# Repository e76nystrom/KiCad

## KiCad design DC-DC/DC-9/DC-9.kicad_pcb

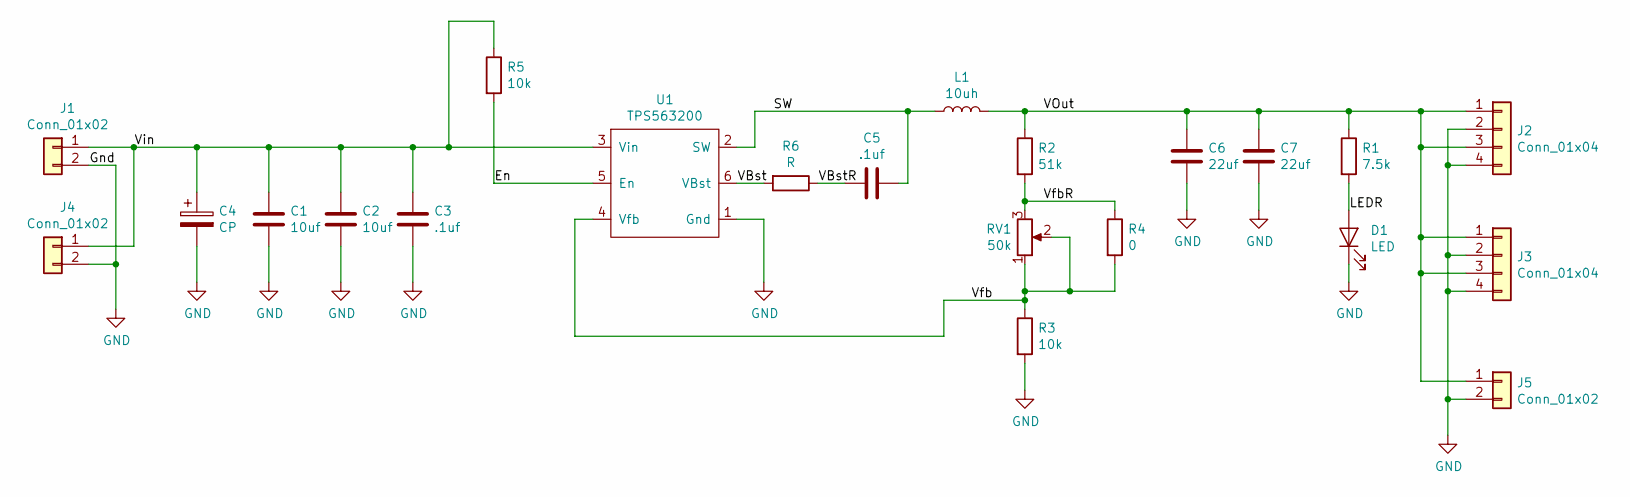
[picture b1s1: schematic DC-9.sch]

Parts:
C1, C2: 10uf; C_0603_1608Metric_Pad1.05x0.95mm_HandSolder
C3, C5: .1uf; C_0805_2012Metric_Pad1.15x1.40mm_HandSolder
C4: CP; CP_Radial_D10.0mm_P5.00mm
C6, C7: 22uf; C_1206_3216Metric_Pad1.42x1.75mm_HandSolder
D1: LED; LED_0805_2012Metric_Pad1.15x1.40mm_HandSolder
J1: Conn_01x02; 2 Pin 3.81mm
J2, J3: Conn_01x04; 4 Pin 3.81mm
J4, J5: Conn_01x02; PinHeader_1x02_P2.54mm_Vertical
L1: 10uh; SRU1038
R1: 7.5k; R_0805_2012Metric_Pad1.15x1.40mm_HandSolder
R2: 51k; R_0805_2012Metric_Pad1.15x1.40mm_HandSolder
R3: 10k; R_0603_1608Metric_Pad1.05x0.95mm_HandSolder
R4: 0; R_0603_1608Metric_Pad1.05x0.95mm_HandSolder
R5: 10k; R_0805_2012Metric_Pad1.15x1.40mm_HandSolder
R6: R; R_0805_2012Metric_Pad1.15x1.40mm_HandSolder
RV1: 50k; Potentiometer_Bourns_3296W_Vertical
U1: TPS563200; SOT-23-6_Handsoldering

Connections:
/En: R5.2, U1.5 (En)
/LEDR: D1.2 (A), R1.2
/SW: C5.1, L1.1, U1.2 (SW)
/VBst: R6.2, U1.6 (VBst)
/VBstR: C5.2, R6.1
/VOut: C6.1, C7.1, J2.1, J2.3, J3.1, J3.3, J5.1, L1.2, R1.1, R2.1
/Vfb: R3.1, R4.2, RV1.1, RV1.2, U1.4 (Vfb)
/VfbR: R2.2, R4.1, RV1.3
/Vin: C1.1, C2.1, C3.1, C4.1, J1.1, J4.1, R5.1, U1.3 (Vin)
GND: C1.2, C2.2, C3.2, C4.2, C6.2, C7.2, D1.1 (K), J1.2, J2.2, J2.4, J3.2, J3.4, J4.2, J5.2, R3.2, U1.1 (Gnd)

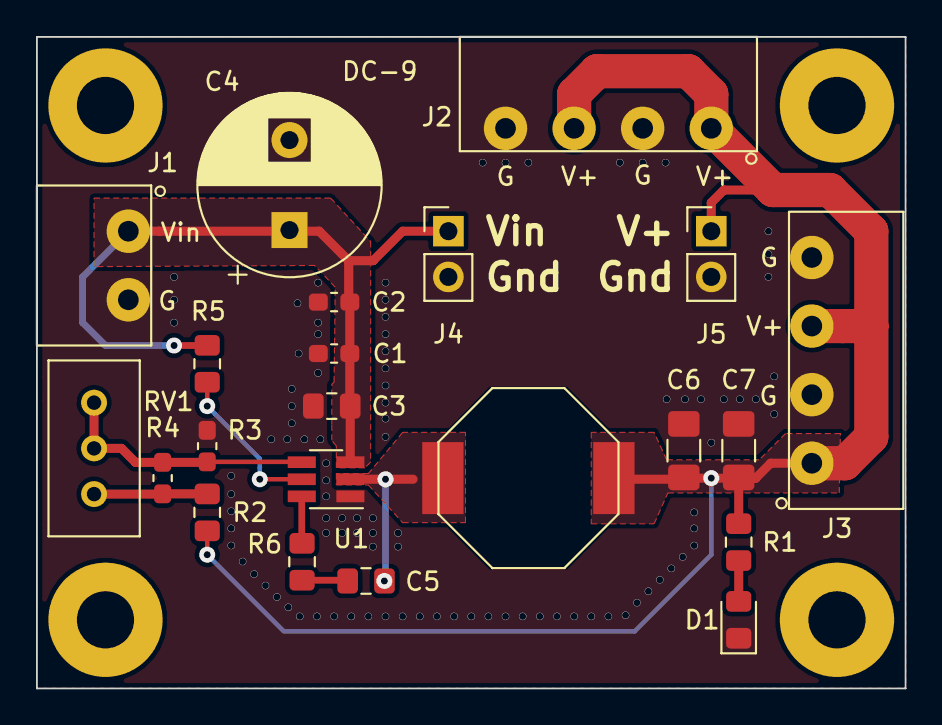
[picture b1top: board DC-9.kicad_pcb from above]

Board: 2 copper layers, 48.3 x 36.2 mm, 22 parts (0 on the bottom side), 10 nets.

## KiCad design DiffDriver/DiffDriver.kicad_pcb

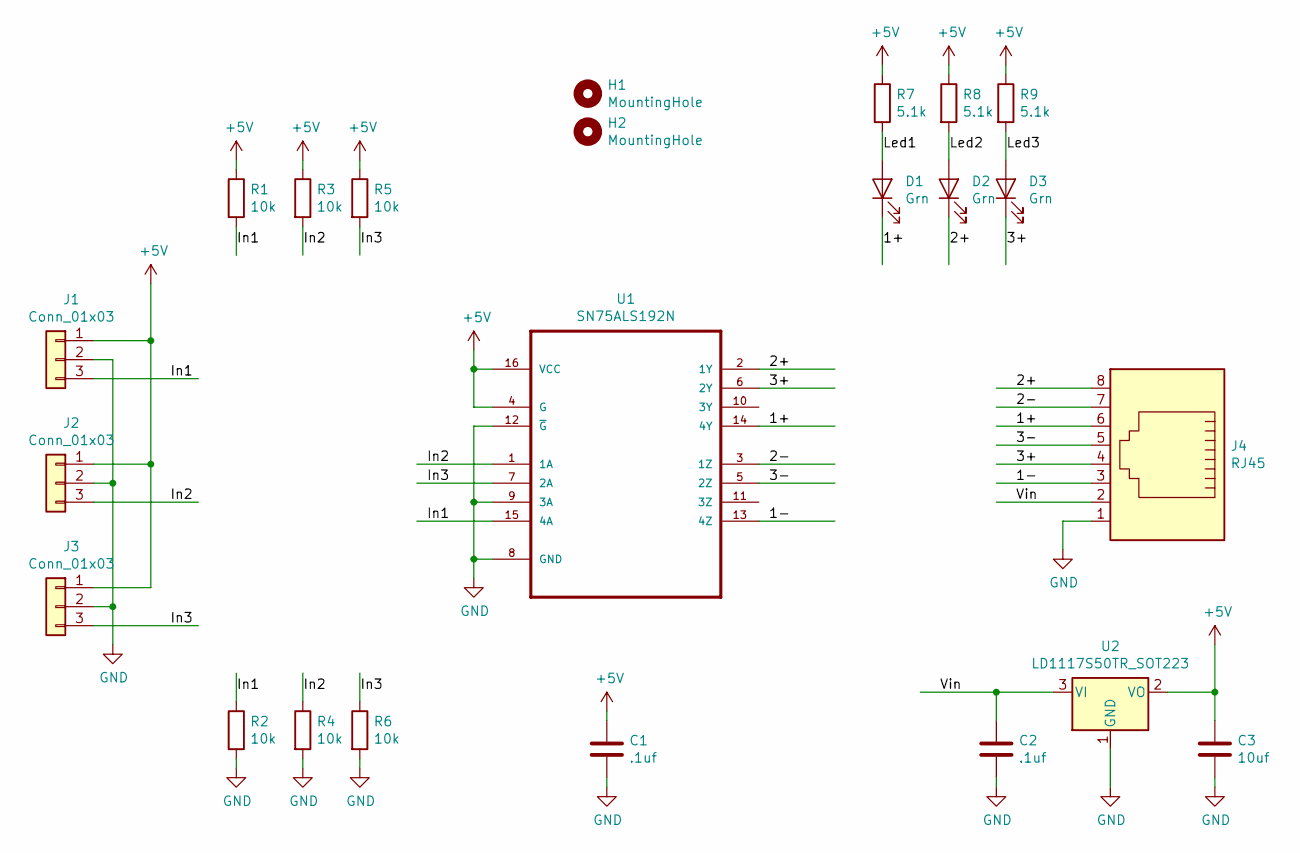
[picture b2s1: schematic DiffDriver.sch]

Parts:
C1, C2: .1uf; C_0805_2012Metric_Pad1.15x1.40mm_HandSolder
C3: 10uf; C_0805_2012Metric_Pad1.15x1.40mm_HandSolder
D1, D2, D3: Grn; LED_0805_2012Metric_Pad1.15x1.40mm_HandSolder
H1, H2: MountingHole; MountingHole _1-8_1-4
J1, J2, J3: Conn_01x03; JST_EH_S3B-EH_1x03_P2.50mm_Horizontal
J4: RJ45; RJ45_Amphenol_54602-x08_Horizontal
R1, R2, R3, R4, R5, R6: 10k; R_0805_2012Metric_Pad1.15x1.40mm_HandSolder
R7, R8, R9: 5.1k; R_0805_2012Metric_Pad1.15x1.40mm_HandSolder
U1: SN75ALS192N; SOIC-16_3.9x9.9mm_P1.27mm
U2: LD1117S50TR_SOT223; SOT-223-3_TabPin2

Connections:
+5V: C1.1, C3.1, J1.1, J2.1, J3.1, R1.1, R3.1, R5.1, R7.1, R8.1, R9.1, U1.4 (G), U1.16 (VCC), U2.2 (VO)
/1+: D1.1 (K), J4.6, U1.14 (4Y)
/1-: J4.3, U1.13 (4Z)
/2+: D2.1 (K), J4.8, U1.2 (1Y)
/2-: J4.7, U1.3 (1Z)
/3+: D3.1 (K), J4.4, U1.6 (2Y)
/3-: J4.5, U1.5 (2Z)
/In1: J1.3, R1.2, R2.1, U1.15 (4A)
/In2: J2.3, R3.2, R4.1, U1.1 (1A)
/In3: J3.3, R5.2, R6.1, U1.7 (2A)
/Led1: D1.2 (A), R7.2
/Led2: D2.2 (A), R8.2
/Led3: D3.2 (A), R9.2
/Vin: C2.1, J4.2, U2.3 (VI)
GND: C1.2, C2.2, C3.2, J1.2, J2.2, J3.2, J4.1, R2.2, R4.2, R6.2, U1.8 (GND), U1.9 (3A), U1.12 (~G), U2.1 (GND)

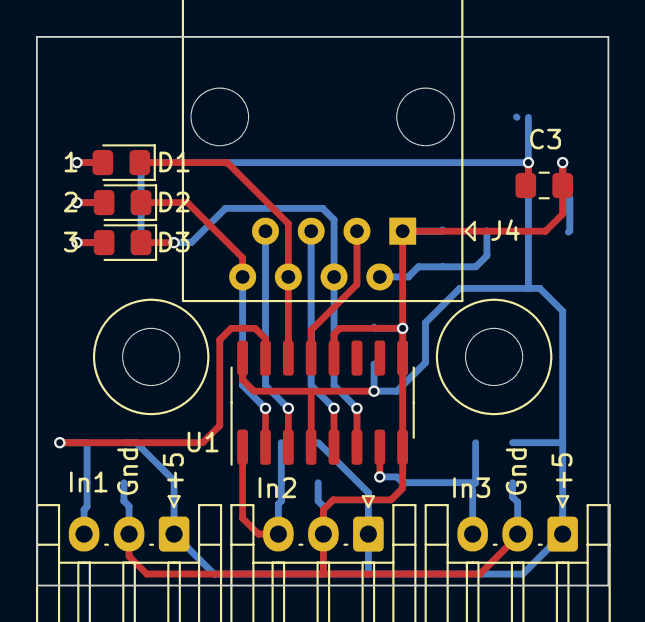
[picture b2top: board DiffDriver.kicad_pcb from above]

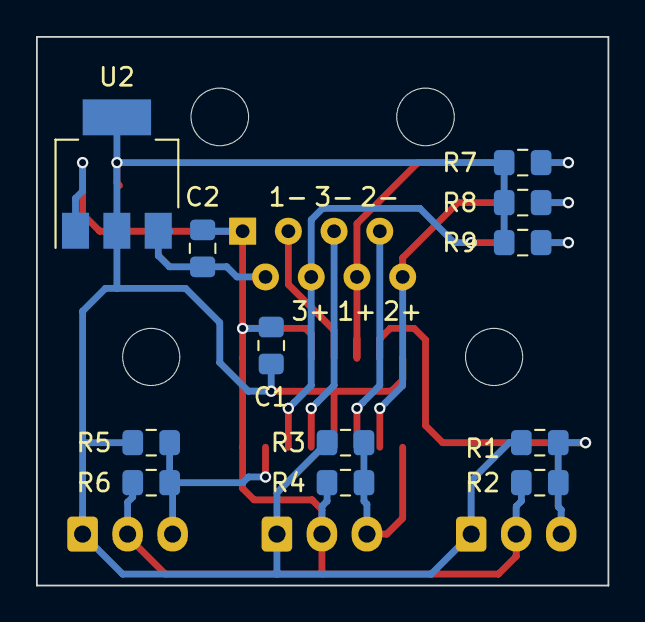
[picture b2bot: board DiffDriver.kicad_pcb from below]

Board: 2 copper layers, 31.8 x 30.5 mm, 23 parts (12 on the bottom side), 15 nets.

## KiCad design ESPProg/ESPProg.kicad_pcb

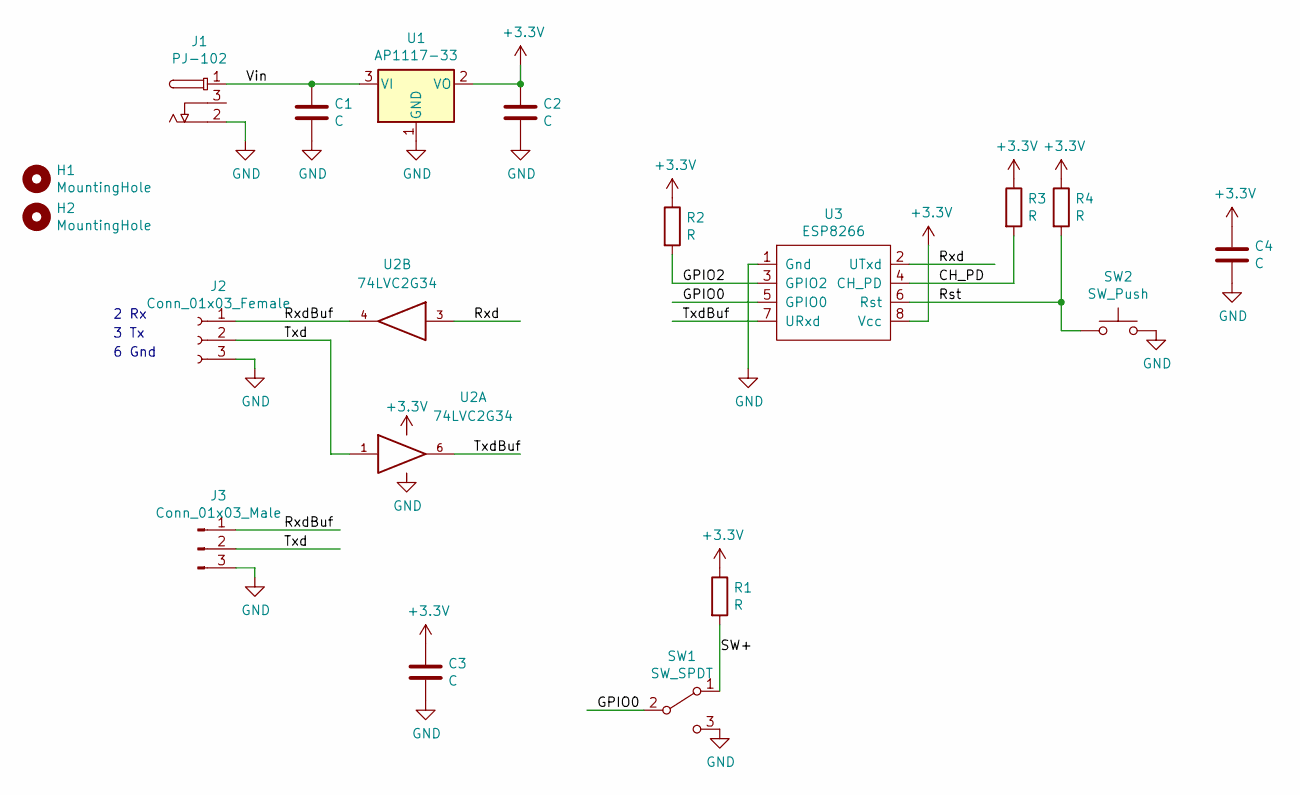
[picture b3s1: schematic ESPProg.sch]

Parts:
C1, C2, C3, C4: C; C_0805_2012Metric_Pad1.15x1.40mm_HandSolder
H1, H2: MountingHole; MountingHole _1-8_1-4
J1: PJ-102; PJ-102-3.81mm
J2: Conn_01x03_Female; JST_EH_S3B-EH_1x03_P2.50mm_Horizontal
J3: Conn_01x03_Male; PinHeader_1x03_P2.54mm_Vertical
R1, R2, R3, R4: R; R_0805_2012Metric_Pad1.15x1.40mm_HandSolder
SW1: SW_SPDT; SlideSW
SW2: SW_Push; PB_PTS-647
U1: AP1117-33; SOT-223-3_TabPin2
U2: 74LVC2G34; SOT-23-6_Handsoldering
U3: ESP8266; ESP-01

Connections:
+3V3: C2.1, C3.1, C4.1, R1.1, R2.1, R3.1, R4.1, U1.2 (VO), U2.5 (VCC), U3.8 (Vcc)
/CH_PD: R3.2, U3.4 (CH_PD)
/GPIO0: SW1.2 (B), U3.5 (GPIO0)
/GPIO2: R2.2, U3.3 (GPIO2)
/Rst: R4.2, SW2.1, U3.6 (Rst)
/Rxd: U2.3, U3.2 (UTxd)
/RxdBuf: J2.1, J3.1, U2.4
/SW+: R1.2, SW1.1 (A)
/Txd: J2.2, J3.2, U2.1
/TxdBuf: U2.6, U3.7 (URxd)
/Vin: C1.1, J1.1, U1.3 (VI)
GND: C1.2, C2.2, C3.2, C4.2, J1.2, J2.3, J3.3, SW1.3 (C), SW2.2, U1.1 (GND), U2.2 (GND), U3.1 (Gnd)

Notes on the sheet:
2 Rx
3 Tx
6 Gnd

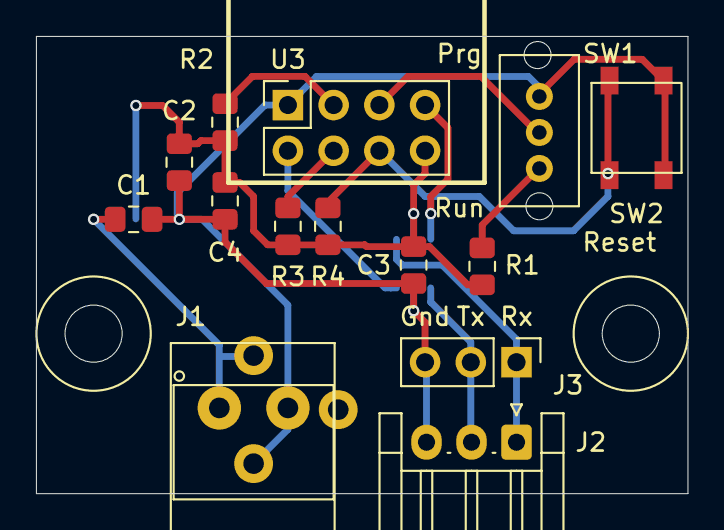
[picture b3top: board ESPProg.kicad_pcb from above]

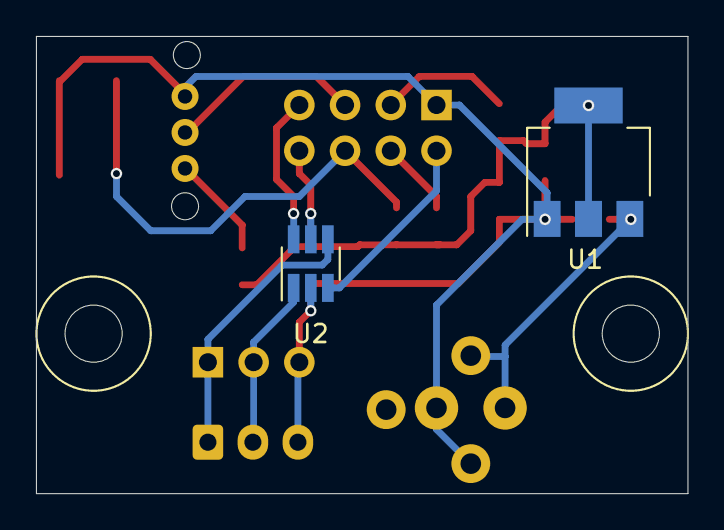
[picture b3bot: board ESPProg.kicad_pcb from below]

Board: 2 copper layers, 36.2 x 25.4 mm, 18 parts (2 on the bottom side), 12 nets.

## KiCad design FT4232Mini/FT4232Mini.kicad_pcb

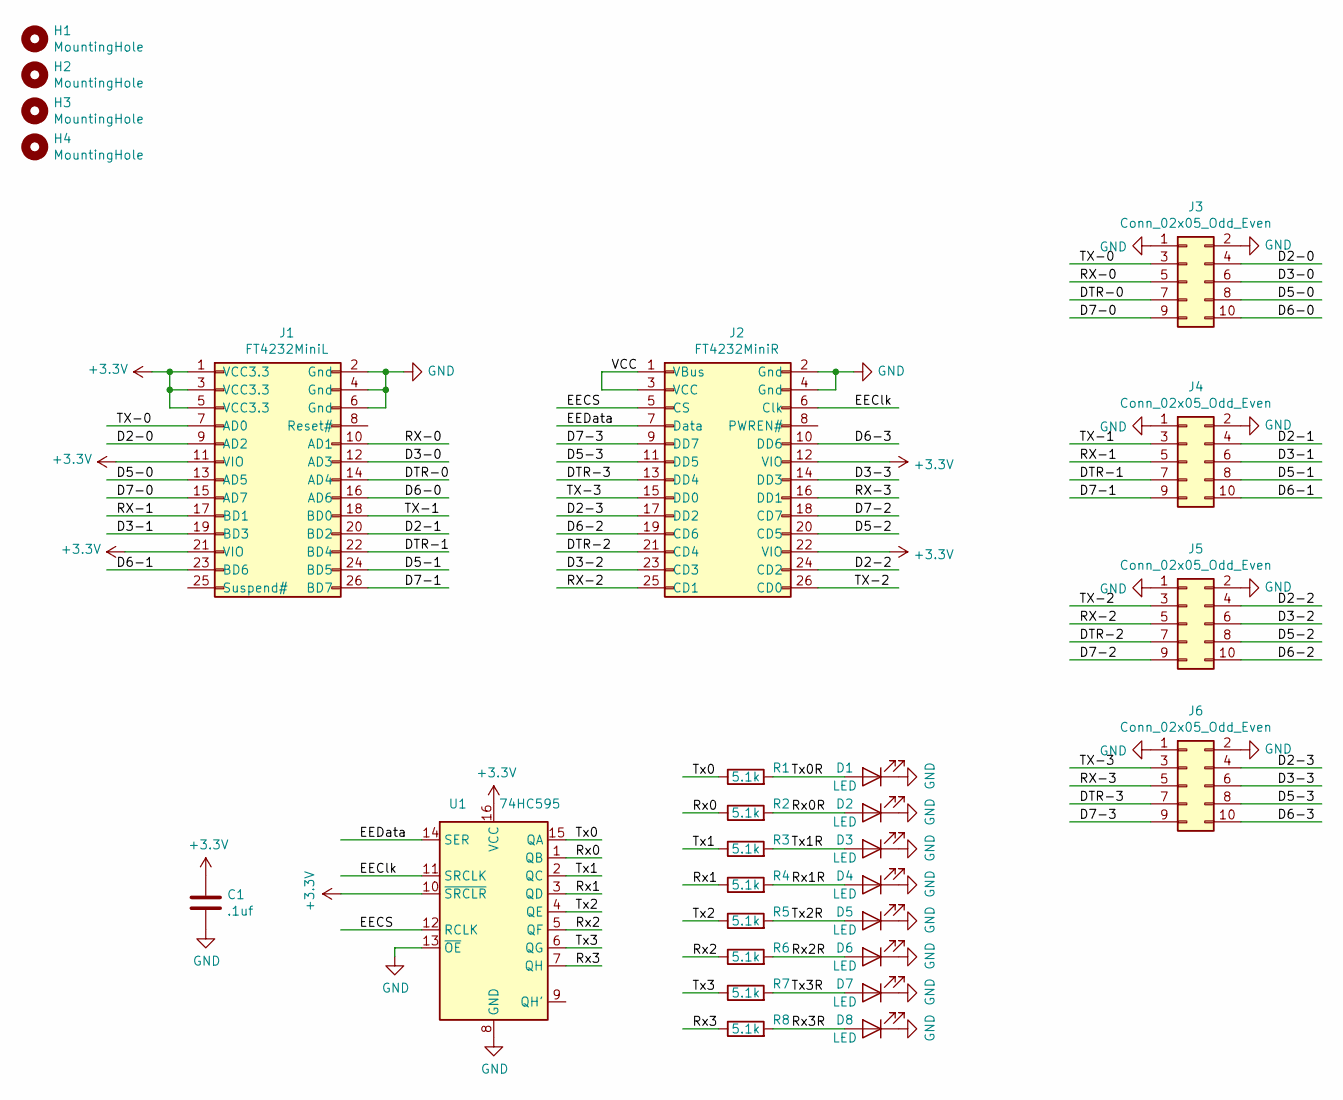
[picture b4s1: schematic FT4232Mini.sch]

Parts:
C1: .1uf; C_0603_1608Metric_Pad1.05x0.95mm_HandSolder
D1, D2, D3, D4, D5, D6, D7, D8: LED; LED_0603_1608Metric_Pad1.05x1.35mm_HandSolder
H1, H2, H3, H4: MountingHole; MountingHole _1-8_1-4
J1: FT4232MiniL; PinHeader_2x13_P2.54mm_Vertical
J2: FT4232MiniR; PinHeader_2x13_P2.54mm_Vertical
J3, J4, J5, J6: Conn_02x05_Odd_Even; PinHeader_2x05_P2.54mm_Vertical
R1, R2, R3, R4, R5, R6, R7, R8: 5.1k; R_0603_1608Metric_Pad1.05x0.95mm_HandSolder
U1: 74HC595; SOIC-16_3.9x9.9mm_P1.27mm

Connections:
+3V3: C1.2, J1.1 (VCC3.3), J1.3 (VCC3.3), J1.5 (VCC3.3), J1.11 (VIO), J1.21 (VIO), J2.12 (VIO), J2.22 (VIO), U1.10 (~SRCLR), U1.16 (VCC)
/D2-0: J1.9 (AD2), J3.4
/D2-1: J1.20 (BD2), J4.4
/D2-2: J2.24 (CD2), J5.4
/D2-3: J2.17 (DD2), J6.4
/D3-0: J1.12 (AD3), J3.6
/D3-1: J1.19 (BD3), J4.6
/D3-2: J2.23 (CD3), J5.6
/D3-3: J2.14 (DD3), J6.6
/D5-0: J1.13 (AD5), J3.8
/D5-1: J1.24 (BD5), J4.8
/D5-2: J2.20 (CD5), J5.8
/D5-3: J2.11 (DD5), J6.8
/D6-0: J1.16 (AD6), J3.10
/D6-1: J1.23 (BD6), J4.10
/D6-2: J2.19 (CD6), J5.10
/D6-3: J2.10 (DD6), J6.10
/D7-0: J1.15 (AD7), J3.9
/D7-1: J1.26 (BD7), J4.9
/D7-2: J2.18 (CD7), J5.9
/D7-3: J2.9 (DD7), J6.9
/DTR-0: J1.14 (AD4), J3.7
/DTR-1: J1.22 (BD4), J4.7
/DTR-2: J2.21 (CD4), J5.7
/DTR-3: J2.13 (DD4), J6.7
/EECS: J2.5 (CS), U1.12 (RCLK)
/EEClk: J2.6 (Clk), U1.11 (SRCLK)
/EEData: J2.7 (Data), U1.14 (SER)
/RX-0: J1.10 (AD1), J3.5
/RX-1: J1.17 (BD1), J4.5
/RX-2: J2.25 (CD1), J5.5
/RX-3: J2.16 (DD1), J6.5
/Rx0: R2.1, U1.1 (QB)
/Rx0R: D2.2 (A), R2.2
/Rx1: R4.1, U1.3 (QD)
/Rx1R: D4.2 (A), R4.2
/Rx2: R6.1, U1.5 (QF)
/Rx2R: D6.2 (A), R6.2
/Rx3: R8.1, U1.7 (QH)
/Rx3R: D8.2 (A), R8.2
/TX-0: J1.7 (AD0), J3.3
/TX-1: J1.18 (BD0), J4.3
/TX-2: J2.26 (CD0), J5.3
/TX-3: J2.15 (DD0), J6.3
/Tx0: R1.1, U1.15 (QA)
/Tx0R: D1.2 (A), R1.2
/Tx1: R3.1, U1.2 (QC)
/Tx1R: D3.2 (A), R3.2
/Tx2: R5.1, U1.4 (QE)
/Tx2R: D5.2 (A), R5.2
/Tx3: R7.1, U1.6 (QG)
/Tx3R: D7.2 (A), R7.2
/VCC: J2.1 (VBus), J2.3 (VCC)
GND: C1.1, D1.1 (K), D2.1 (K), D3.1 (K), D4.1 (K), D5.1 (K), D6.1 (K), D7.1 (K), D8.1 (K), J1.2 (Gnd), J1.4 (Gnd), J1.6 (Gnd), J2.2 (Gnd), J2.4 (Gnd), J3.1, J3.2, J4.1, J4.2, J5.1, J5.2, J6.1, J6.2, U1.8 (GND), U1.13 (~OE)

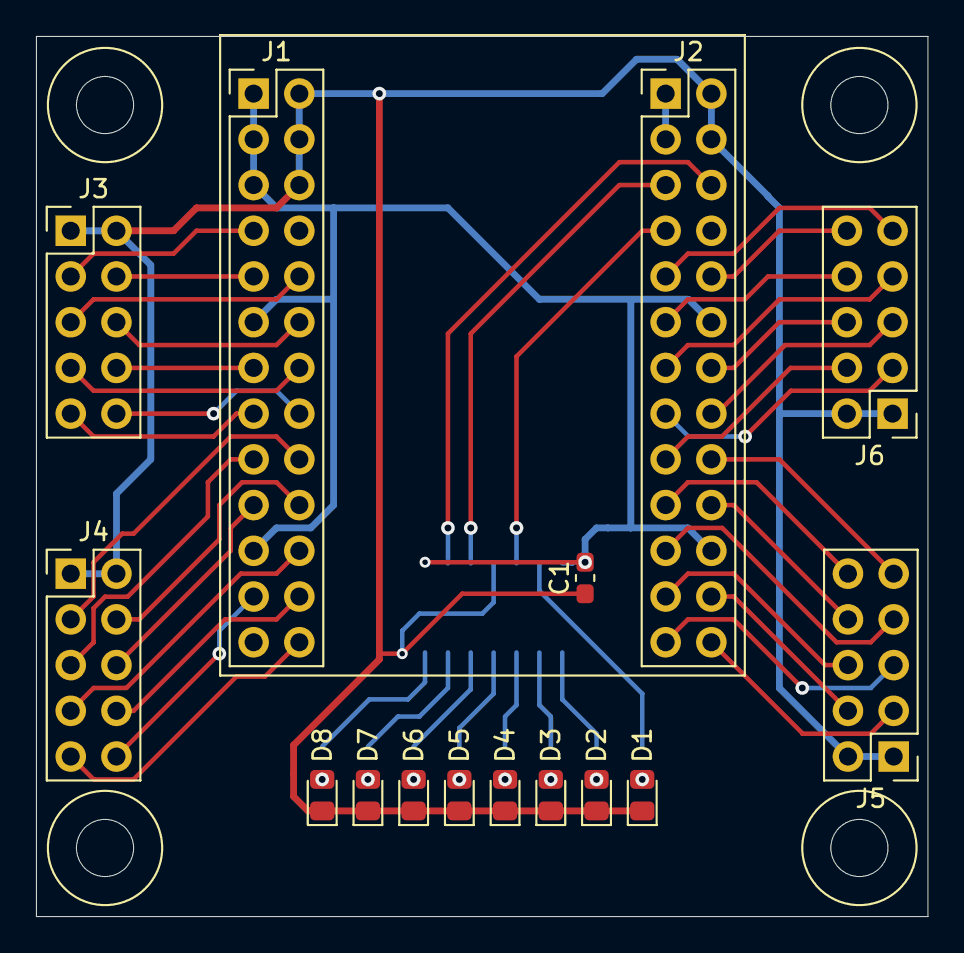
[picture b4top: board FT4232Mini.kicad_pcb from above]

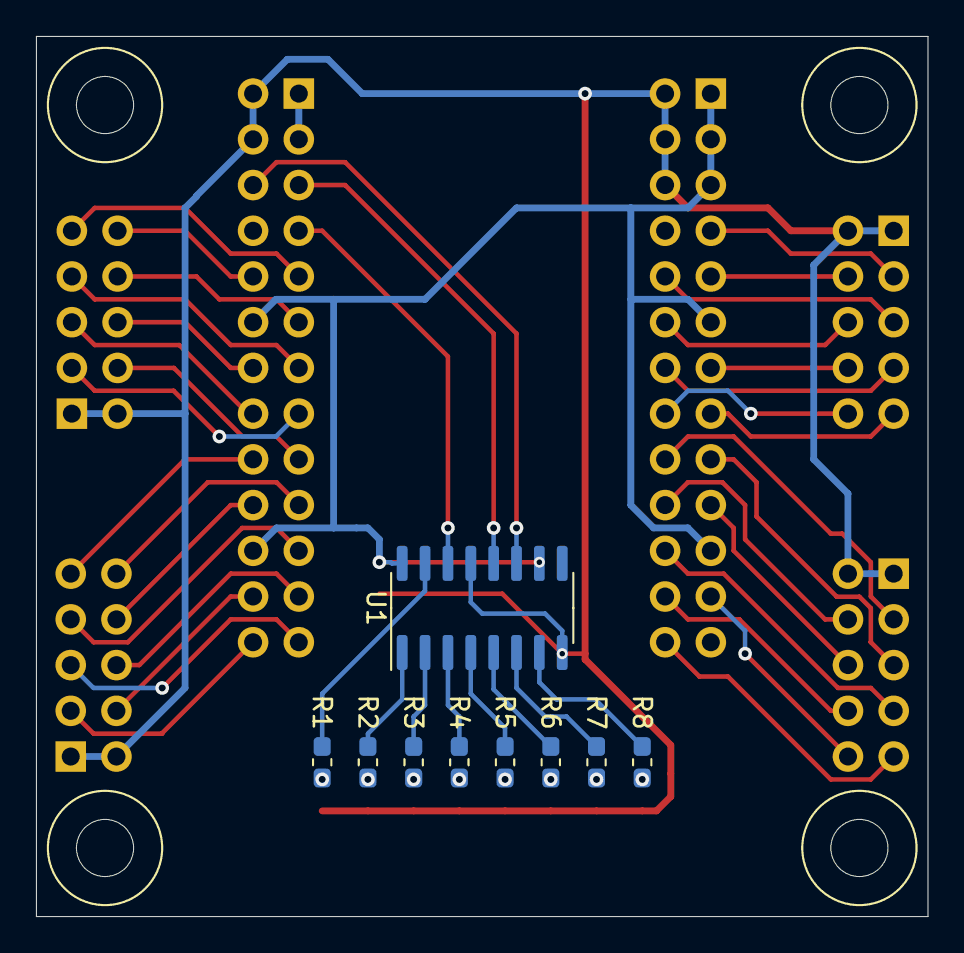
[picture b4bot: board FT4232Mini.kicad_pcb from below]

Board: 2 copper layers, 49.5 x 48.9 mm, 28 parts (9 on the bottom side), 54 nets.

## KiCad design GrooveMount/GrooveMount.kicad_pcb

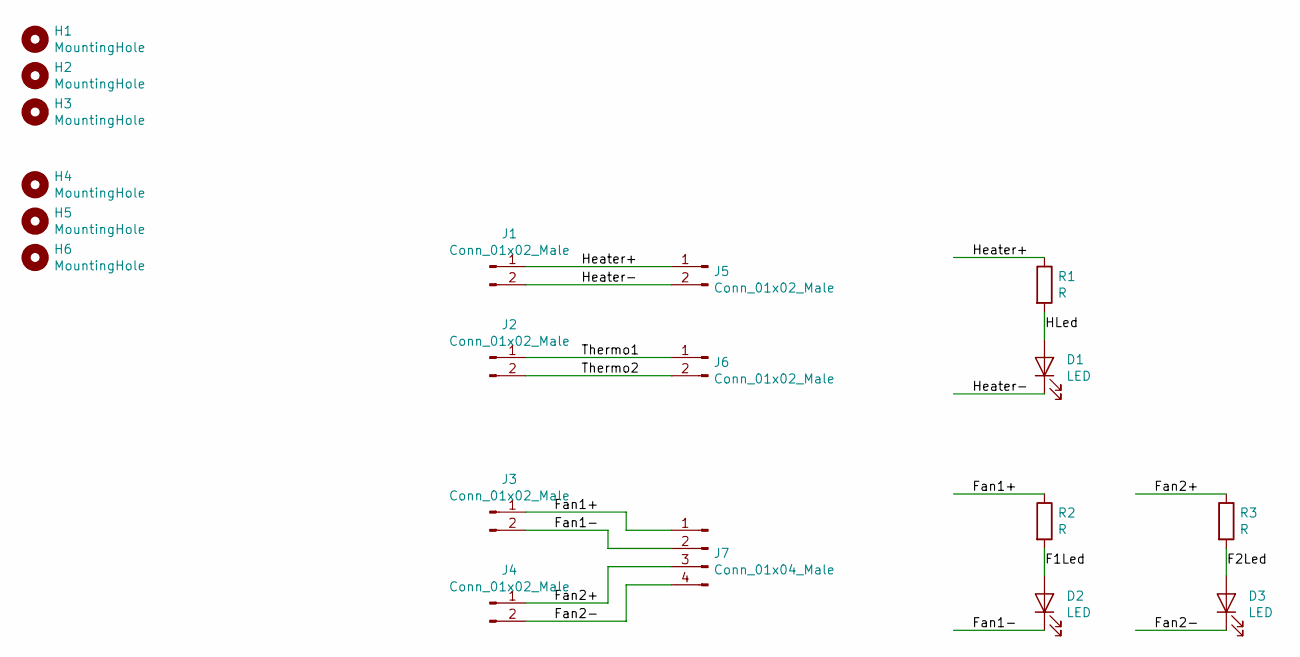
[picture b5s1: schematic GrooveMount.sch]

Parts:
D1, D2, D3: LED; LED_0805_2012Metric_Pad1.15x1.40mm_HandSolder
H1, H2, H3: MountingHole; MountingHole _1-8_1-4
H4, H5, H6: MountingHole; MountingHole_6-32_3-8
J1, J2: Conn_01x02_Male; PhoenixContact_MCV_1,5_2-G-3.81_1x02_P3.81mm_Vertical
J3, J4: Conn_01x02_Male; JST_EH_B2B-EH-A_1x02_P2.50mm_Vertical
J5: Conn_01x02_Male; 2_Pin_5mm
J6: Conn_01x02_Male; PinHeader_1x02_P2.54mm_Vertical
J7: Conn_01x04_Male; PinHeader_1x04_P2.54mm_Vertical
R1, R2, R3: R; R_0805_2012Metric_Pad1.15x1.40mm_HandSolder

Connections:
/F1Led: D2.2 (A), R2.2
/F2Led: D3.2 (A), R3.2
/Fan1+: J3.1, J7.1, R2.1
/Fan1-: D2.1 (K), J3.2, J7.2
/Fan2+: J4.1, J7.3, R3.1
/Fan2-: D3.1 (K), J4.2, J7.4
/HLed: D1.2 (A), R1.2
/Heater+: J1.1, J5.1, R1.1
/Heater-: D1.1 (K), J1.2, J5.2
/Thermo1: J2.1, J6.1
/Thermo2: J2.2, J6.2

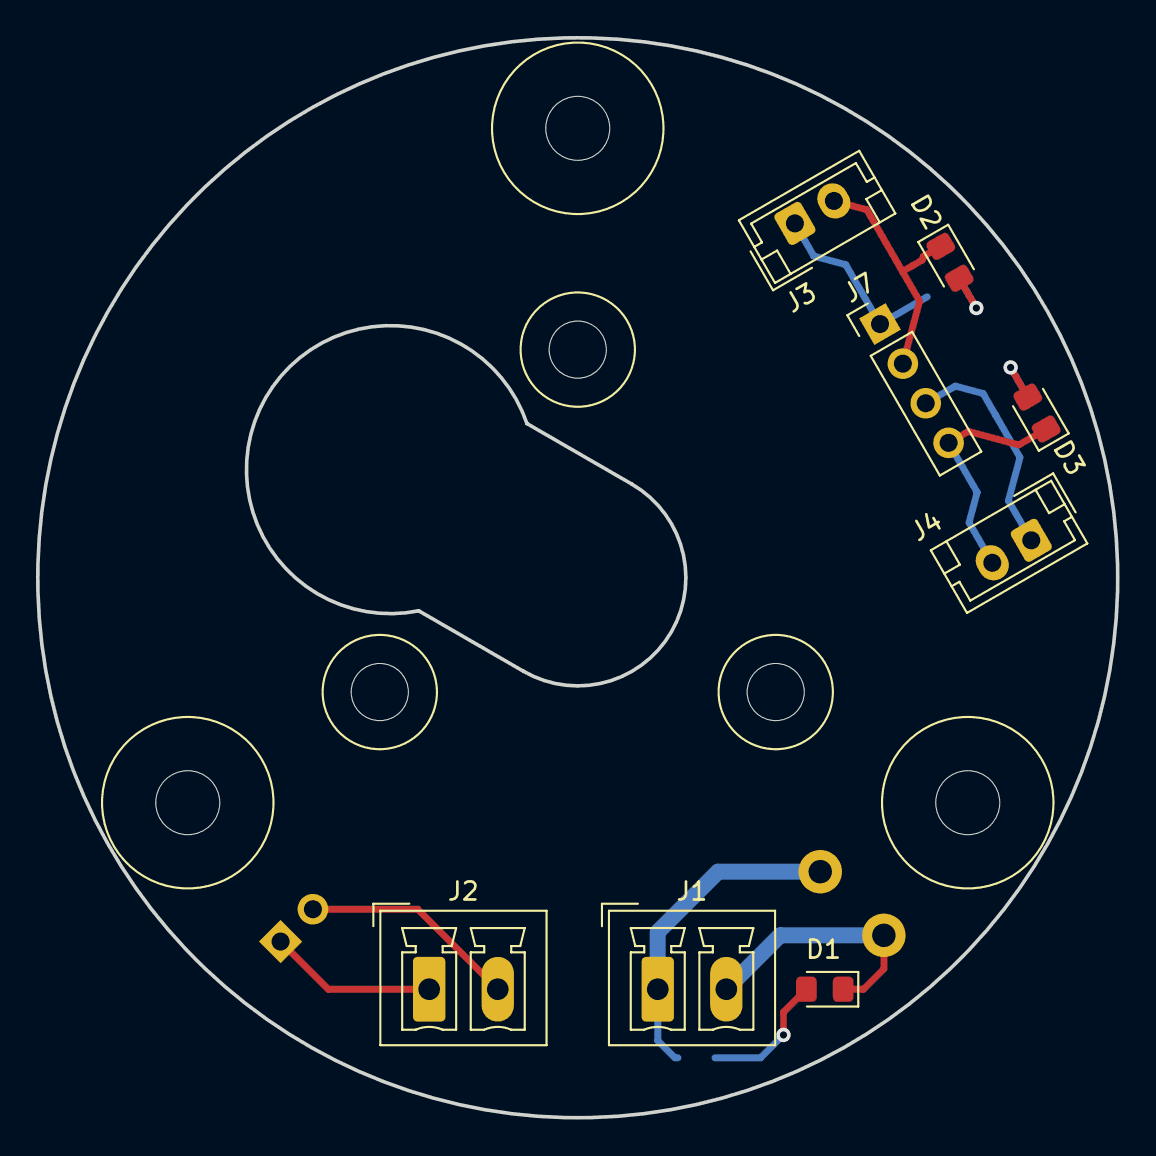
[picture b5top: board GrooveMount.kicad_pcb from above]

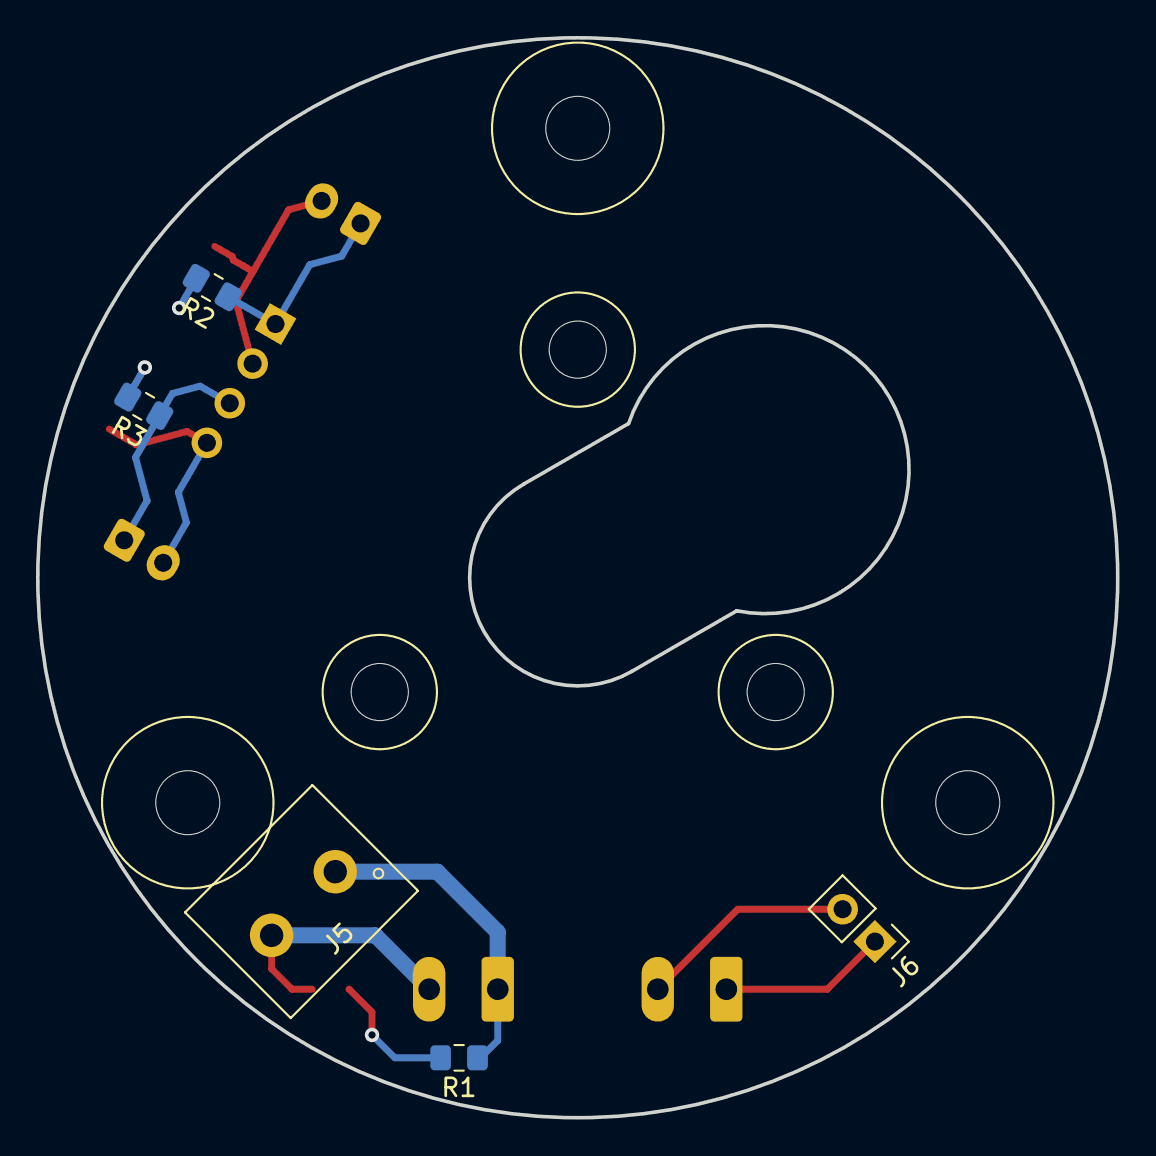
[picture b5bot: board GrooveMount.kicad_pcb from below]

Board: 2 copper layers, 60.0 x 60.0 mm, 19 parts (5 on the bottom side), 11 nets.

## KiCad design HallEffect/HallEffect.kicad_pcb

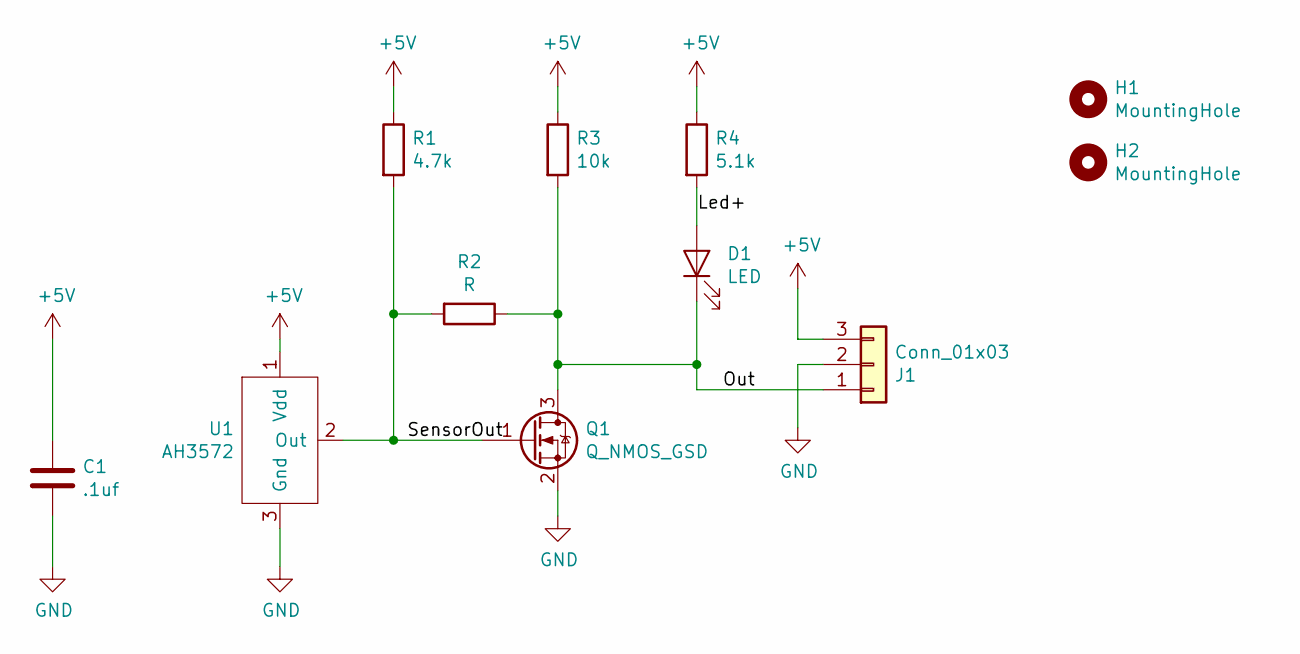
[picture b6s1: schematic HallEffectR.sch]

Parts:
C1: .1uf; C_0805_2012Metric_Pad1.15x1.40mm_HandSolder
D1: LED; LED_0805_2012Metric_Pad1.15x1.40mm_HandSolder
H1, H2: MountingHole; MountingHole _1-8_1-4
J1: Conn_01x03; JST_EH_S3B-EH_1x03_P2.50mm_Horizontal
Q1: Q_NMOS_GSD; SOT-23
R1: 4.7k; R_0805_2012Metric_Pad1.15x1.40mm_HandSolder
R2: R; R_0603_1608Metric_Pad1.05x0.95mm_HandSolder
R3: 10k; R_0805_2012Metric_Pad1.15x1.40mm_HandSolder
R4: 5.1k; R_0805_2012Metric_Pad1.15x1.40mm_HandSolder
U1: AH3572; SOT-23

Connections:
+5V: C1.1, J1.3, R1.1, R3.1, R4.1, U1.1 (Vdd)
/Led+: D1.2 (A), R4.2
/Out: D1.1 (K), J1.1, Q1.3 (D), R2.1, R3.2
/SensorOut: Q1.1 (G), R1.2, R2.2, U1.2 (Out)
GND: C1.2, J1.2, Q1.2 (S), U1.3 (Gnd)

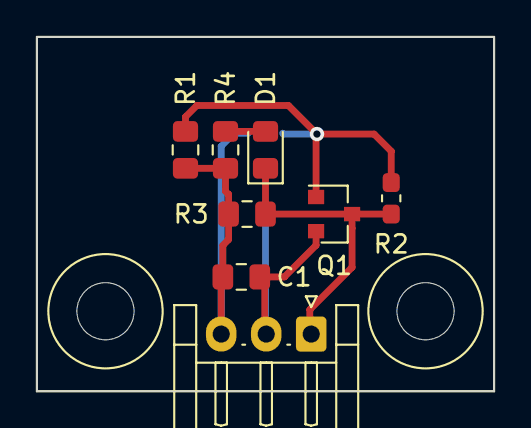
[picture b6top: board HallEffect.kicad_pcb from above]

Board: 2 copper layers, 25.4 x 19.7 mm, 11 parts (1 on the bottom side), 5 nets.
